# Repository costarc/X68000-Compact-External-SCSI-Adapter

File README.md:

# X68000 Compact external SCSI adapters

Two alternative boards that bring the external half-pitch (MDR 50) SCSI port of the X68000 Compact out to a standard 2x25, 2.54 mm SCSI header. Both follow the half-pitch pinout of the X68000 Book, Appendix D.10. Use one or the other; each folder has its own README with usage instructions, pin table and revision notes.

- [`MDR-50_Male-Male`](MDR-50_Male-Male/README.md) - half-pitch connector on the board.
- [`SCSI-CN50-28AWG`](SCSI-CN50-28AWG/README.md) - solder pads for the wires of a half-pitch plug cable.

Not yet tested on real hardware: check every link with a meter before use. Do not use the Rev 1.0 MDR-50 boards.

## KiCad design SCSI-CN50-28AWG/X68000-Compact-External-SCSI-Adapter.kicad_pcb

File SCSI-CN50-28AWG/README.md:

# X68000 Compact external SCSI adapter - 28 AWG cable board

A board for bringing the external half-pitch (MDR 50) SCSI port of the X68000 Compact out to a standard 2x25, 2.54 mm SCSI header. Instead of a half-pitch connector on the board, **J1 is a block of 2x25 solder holes** for the wires of a 28 AWG cable that ends in a half-pitch 50-pin plug (for example a "CN50P" SCSI cable with soldered MDR plug and bare wires at the other end). The board re-maps the half-pitch pin numbers to ribbon-header numbering.

- **J1** - 2x25 solder holes, one hole per half-pitch pin. Hole numbers are the half-pitch pin numbers (see the table).
- **J2** - 2x25 2.54 mm socket (`PinSocket_2x25_P2.54mm_Horizontal`), standard SCSI-1 ribbon numbering, towards the device.

## How to use

1. Take a cable with a half-pitch 50-pin plug and strip the free end. Identify the wire of each plug pin (use a meter or the cable's colour chart; do not assume the wire order).
2. Solder the wire of plug pin *n* into J1 hole *n*. Pin 13 is not connected on the machine and its hole is also left open. Ground wires (pins 1-12, 14-25, 35, 36, 37, 39, 40, 42) must all be soldered.
3. Power the X68000 off and plug the cable into its external SCSI port.
4. Attach the device to J2 with a 50-pin ribbon cable, red stripe on pin 1.
5. Set up the SCSI bus as usual: unique IDs and termination at both ends. TERMPWR (half-pitch pin 38) is joined to J2 pin 26, so check whether your device expects, supplies or must not receive terminator power.
6. Power on the device first, then the X68000.

Check the links with a meter before first use. This board has not been tested on real hardware.

## Pin mapping

Machine side, half-pitch 50-pin connector (X68000 Book, Appendix D.10) → header side, 2x25 2.54 mm (standard SCSI-1 ribbon numbering):

| Signal | Half-pitch pin | Header pin |
|---|---|---|
| DB0 … DB7 | 26 … 33 | 2, 4, 6, 8, 10, 12, 14, 16 |
| PARITY (DBP) | 34 | 18 |
| TERMPWR (TMPWR) | 38 | 26 |
| /ATN | 41 | 32 |
| /BSY | 43 | 36 |
| /ACK | 44 | 38 |
| /RST | 45 | 40 |
| /MSG | 46 | 42 |
| /SEL | 47 | 44 |
| /C/D | 48 | 46 |
| /REQ | 49 | 48 |
| /I/O | 50 | 50 |
| GND | 1-12, 14-25, 35, 36, 37, 39, 40, 42 | all other pins except 25 |
| not connected | 13 | 25 |

On J1 the solder holes are paired in rows: 1-2, 3-4, ... 49-50 (odd numbers in one column, even in the other); the hole number is the half-pitch pin number. On J2, header pin 1 is the red-stripe side of the ribbon cable.

## Revisions

Rev 2.0 (pin 13 NC)
- J1 pin 13 is no connect (it was tied to ground); J2 unchanged.
- Gerbers: `Fabrication/X68000-Compact-External-SCSI-Adapter Rev 2.0 (pin 13 NC).zip` (earlier: `Rev 2.0.zip`).

Rev 2.0
- Changes to pinout in the X68000 side, as the 2.0mm pin header seem to use a non standard pinout

Rev 1.0
- Based on SCSI pinouts

## Related board

`MDR-50_Male-Male` does the same job with a half-pitch connector on the board instead of solder pads. Use one board or the other.

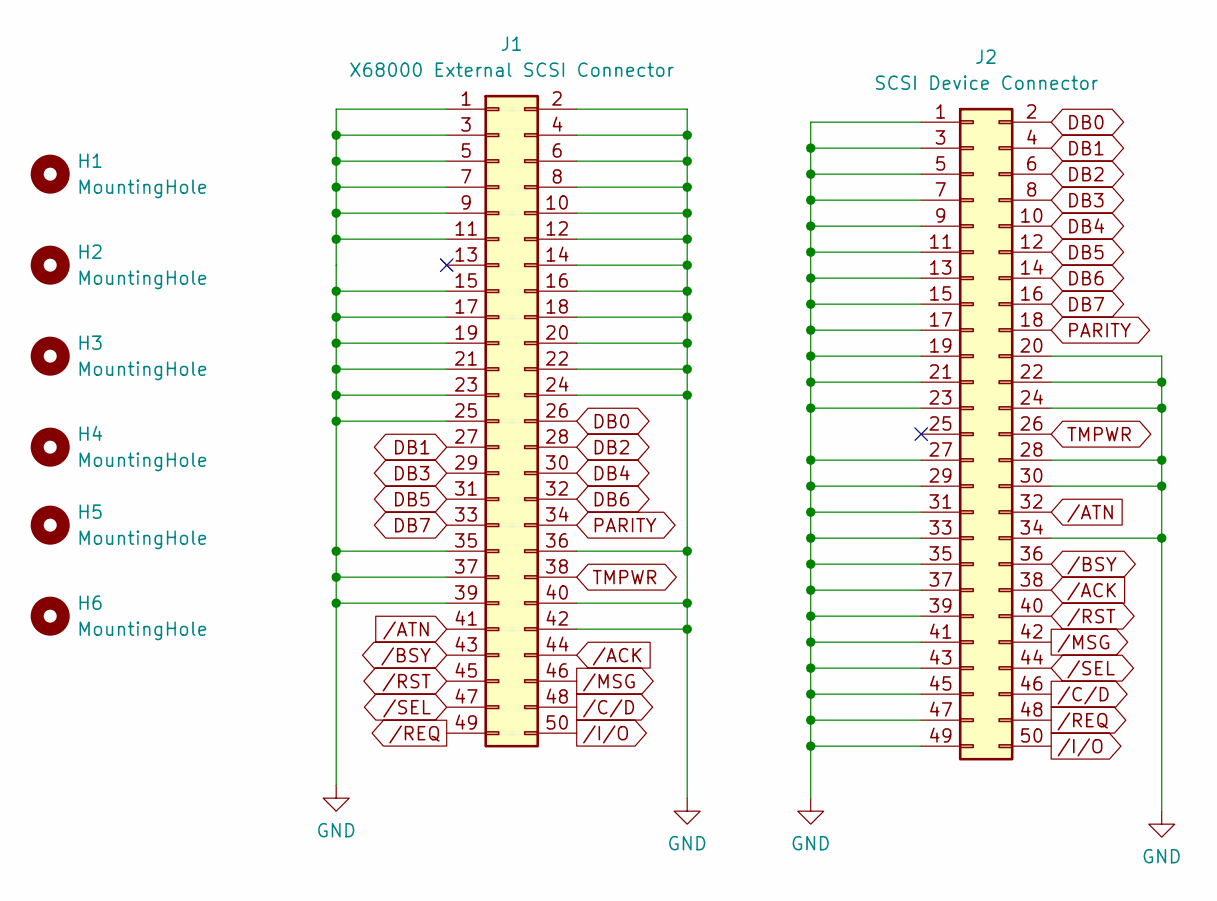
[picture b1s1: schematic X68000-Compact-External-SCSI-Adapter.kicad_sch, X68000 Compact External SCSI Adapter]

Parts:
H1, H2, H3, H4, H5, H6: MountingHole; MountingHole_2.2mm_M2
J1: X68000 External SCSI Connector; SolderHole_2x25_2.5mmx1.6mm
J2: SCSI Device Connector; PinSocket_2x25_P2.54mm_Horizontal

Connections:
DB0: J1.26, J2.2
DB1: J1.27, J2.4
DB2: J1.28, J2.6
DB3: J1.29, J2.8
DB4: J1.30, J2.10
DB5: J1.31, J2.12
DB6: J1.32, J2.14
DB7: J1.33, J2.16
GND: J1.1, J1.2, J1.3, J1.4, J1.5, J1.6, J1.7, J1.8, J1.9, J1.10, J1.11, J1.12, J1.14, J1.15, J1.16, J1.17, J1.18, J1.19, J1.20, J1.21, J1.22, J1.23, J1.24, J1.25, J1.35, J1.36, J1.37, J1.39, J1.40, J1.42, J2.1, J2.3, J2.5, J2.7, J2.9, J2.11, J2.13, J2.15, J2.17, J2.19, J2.20, J2.21, J2.22, J2.23, J2.24, J2.27, J2.28, J2.29, J2.30, J2.31, J2.33, J2.34, J2.35, J2.37, J2.39, J2.41, J2.43, J2.45, J2.47, J2.49
PARITY: J1.34, J2.18
TMPWR: J1.38, J2.26
/ACK: J1.44, J2.38
/ATN: J1.41, J2.32
/BSY: J1.43, J2.36
/C/D: J1.48, J2.46
/I/O: J1.50, J2.50
/MSG: J1.46, J2.42
/REQ: J1.49, J2.48
/RST: J1.45, J2.40
/SEL: J1.47, J2.44

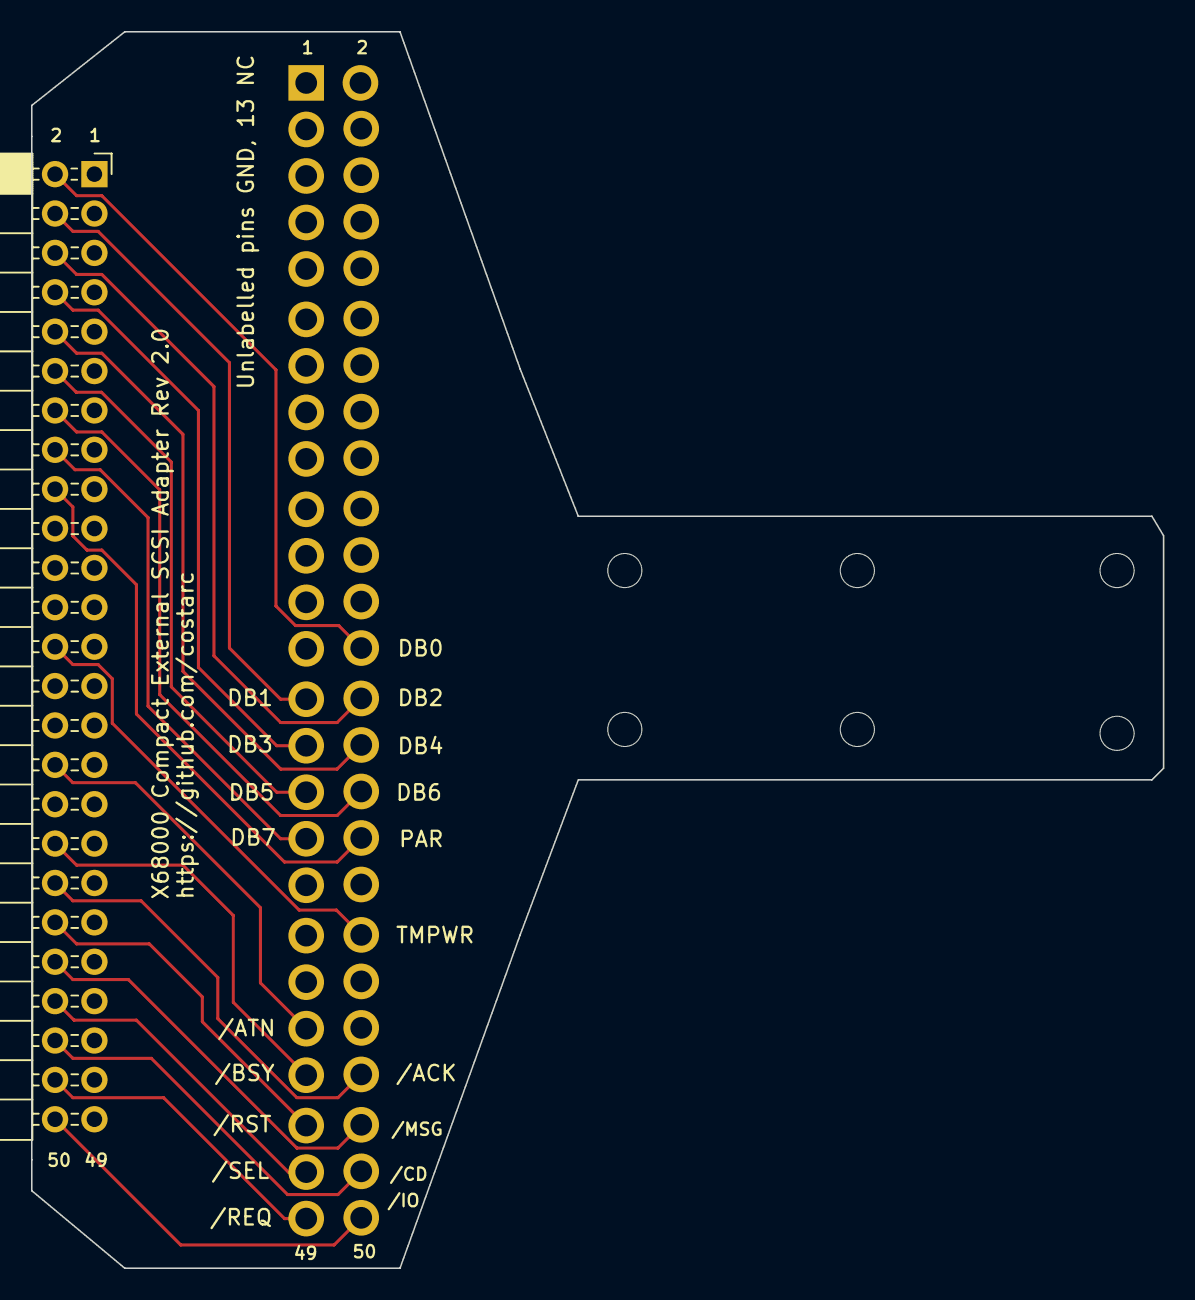
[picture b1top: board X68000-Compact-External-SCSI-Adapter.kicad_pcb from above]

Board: 2 copper layers, 73.0 x 79.8 mm, 8 parts (0 on the bottom side), 20 nets.
